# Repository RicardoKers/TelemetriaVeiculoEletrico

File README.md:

# TelemetriaVeiculoEletrico

Projeto da telemetria do veículo elétrico do IFC Luzerna versão 2022

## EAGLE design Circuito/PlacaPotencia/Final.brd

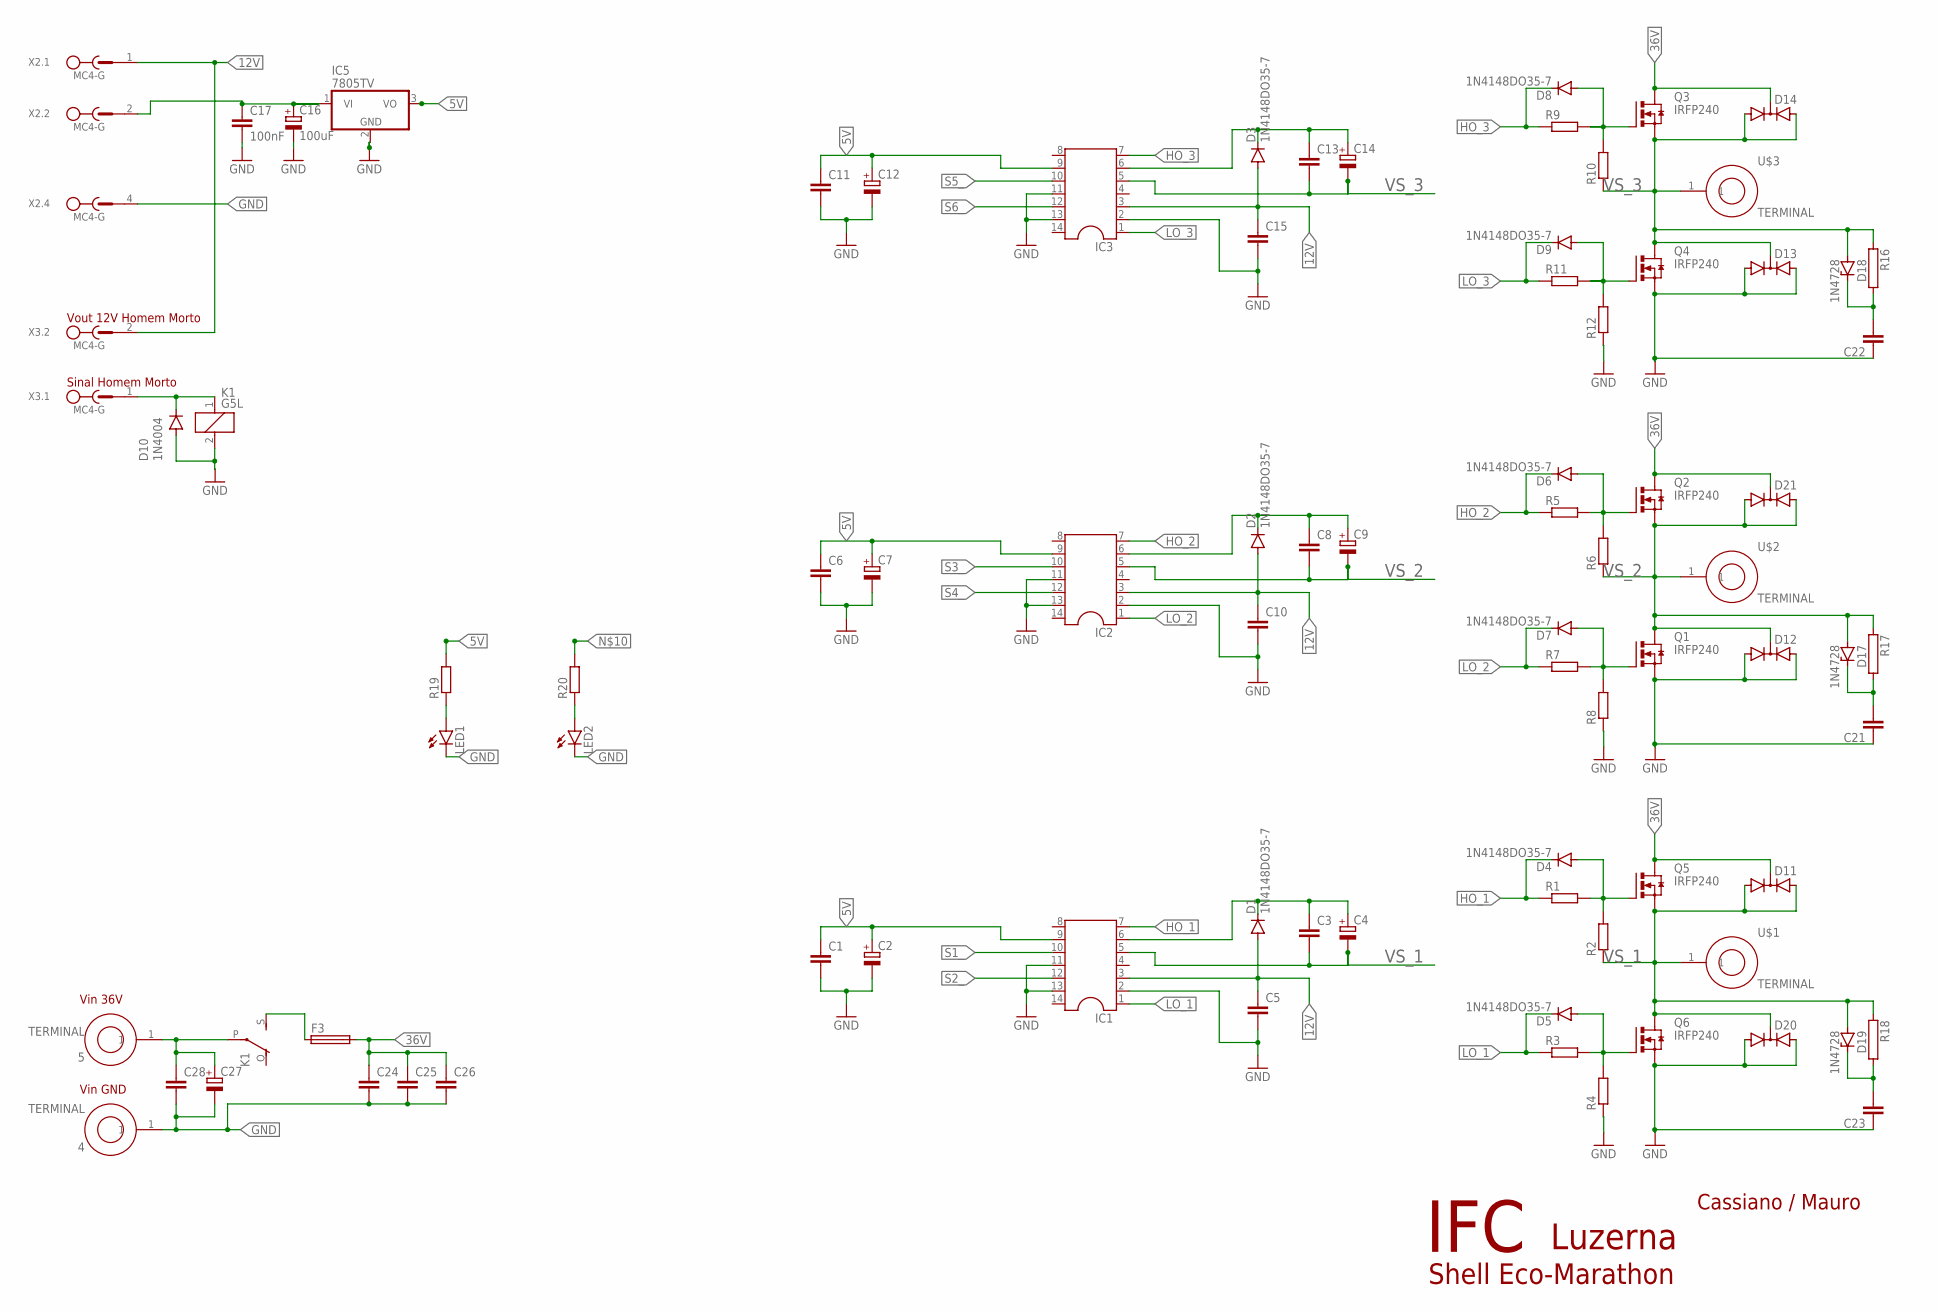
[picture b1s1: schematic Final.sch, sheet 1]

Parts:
4, 5: TERMINAL
C1, C6, C11: C-EU050-045X075; C050-045X075
C2, C4, C7, C9, C12, C14: CPOL-EUE2.5-7; E2,5-7
C3, C5, C8, C10, C13, C15: C-EU050-025X075; C050-025X075
C16: 100uF; E2,5-7
C17: 100nF; C050-045X075
C21, C22, C23: C-EU150-054X183; C150-054X183
C24, C25, C26, C28: C-EU275-093X316; C275-093X316
C27: CPOL-EUE10-22.5; EB22,5D
D1, D2, D3, D4, D5, D6, D7, D8, D9: 1N4148DO35-7; DO35-7
D10: 1N4004; DO41-10
D11, D12, D13, D14, D20, D21: DIODE-2AC|CATO220V; TO220ABS
D17, D18, D19: 1N4728; DO41Z10
F3: SH22,5A
IC1, IC2, IC3: DIL14
IC5: 7805TV; TO220V
K1: G5L; G5LE
LED1, LED2: LED5MM
Q1, Q2, Q3, Q4, Q5, Q6: IRFP240; TO247BV
R1, R2, R3, R4, R5, R6, R7, R8, R9, R10, R11, R12, R19, R20: R-EU_0204/7; 0204/7
R16, R17, R18: RCA4150; CA4150
U$1, U$2, U$3: TERMINAL
X2, X3: MC4-G

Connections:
5V: C1.1, C2.+, C6.1, C7.+, C11.1, C12.+, IC1.9, IC2.9, IC3.9, IC5.3 (VO), R19.2; also elsewhere on the board
12V: C5.1, C10.1, C15.1, D1.A, D2.A, D3.A, IC1.3, IC2.3, IC3.3, X2.1, X3.2
36V: C24.1, C25.1, C26.1, D11.C, D14.C, D21.C, F3.2, Q2.D, Q3.D, Q5.D
GND: 4.1, C1.2, C2.-, C5.2, C6.2, C7.-, C10.2, C11.2, C12.-, C15.2, C16.-, C17.2, C21.1, C22.1, C23.1, C24.2, C25.2, C26.2, C27.-, C28.2, D10.A, D12.A1, D12.A2, D13.A1, D13.A2, D20.A1, D20.A2, IC1.2, IC1.11, IC1.13, IC2.2, IC2.11, IC2.13, IC3.2, IC3.11, IC3.13, IC5.2 (GND), K1.2, LED1.K (C), LED2.K (C), Q1.S, Q4.S, Q6.S, R4.1, R8.1, R12.1, X2.4; also elsewhere on the board
HO_1: D4.C, IC1.7, R1.1
HO_2: D6.C, IC2.7, R5.1
HO_3: D8.C, IC3.7, R9.1
LO_1: D5.C, IC1.1, R3.1
LO_2: D7.C, IC2.1, R7.1
LO_3: D9.C, IC3.1, R11.1
unnamed: D4.A, Q5.G, R1.2, R2.2
unnamed: D5.A, Q6.G, R3.2, R4.2
unnamed: F3.1, K1.S
unnamed: D6.A, Q2.G, R5.2, R6.2
unnamed: D7.A, Q1.G, R7.2, R8.2
unnamed: D8.A, Q3.G, R9.2, R10.2
unnamed: D9.A, Q4.G, R11.2, R12.2
unnamed: C16.+, C17.1, IC5.1 (VI), X2.2
unnamed: D10.C, K1.1, R20.2, X3.1
unnamed: 5.1, C27.+, C28.1, K1.P
unnamed: LED1.A, R19.1
unnamed: LED2.A, R20.1
unnamed: C22.2, D18.C, R16.2
unnamed: C21.2, D17.C, R17.2
unnamed: C23.2, D19.C, R18.2
S1_: IC1.10; also elsewhere on the board
S2_: IC1.12; also elsewhere on the board
S3_: IC2.10; also elsewhere on the board
S4_: IC2.12; also elsewhere on the board
S5_: IC3.10; also elsewhere on the board
S6_: IC3.12; also elsewhere on the board
VB_1: C3.1, C4.+, D1.C, IC1.6
VB_2: C8.1, C9.+, D2.C, IC2.6
VB_3: C13.1, C14.+, D3.C, IC3.6
VS_1: C3.2, C4.-, D11.A1, D11.A2, D19.A, D20.C, IC1.5, Q5.S, Q6.D, R2.1, R18.1, U$1.1
VS_2: C8.2, C9.-, D12.C, D17.A, D21.A1, D21.A2, IC2.5, Q1.D, Q2.S, R6.1, R17.1, U$2.1
VS_3: C13.2, C14.-, D13.C, D14.A1, D14.A2, D18.A, IC3.5, Q3.S, Q4.D, R10.1, R16.1, U$3.1

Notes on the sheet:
Vout 12V Homem Morto
Sinal Homem Morto
Vin 36V
Vin GND
Shell Eco-Marathon
Cassiano / Mauro
IFC
Luzerna

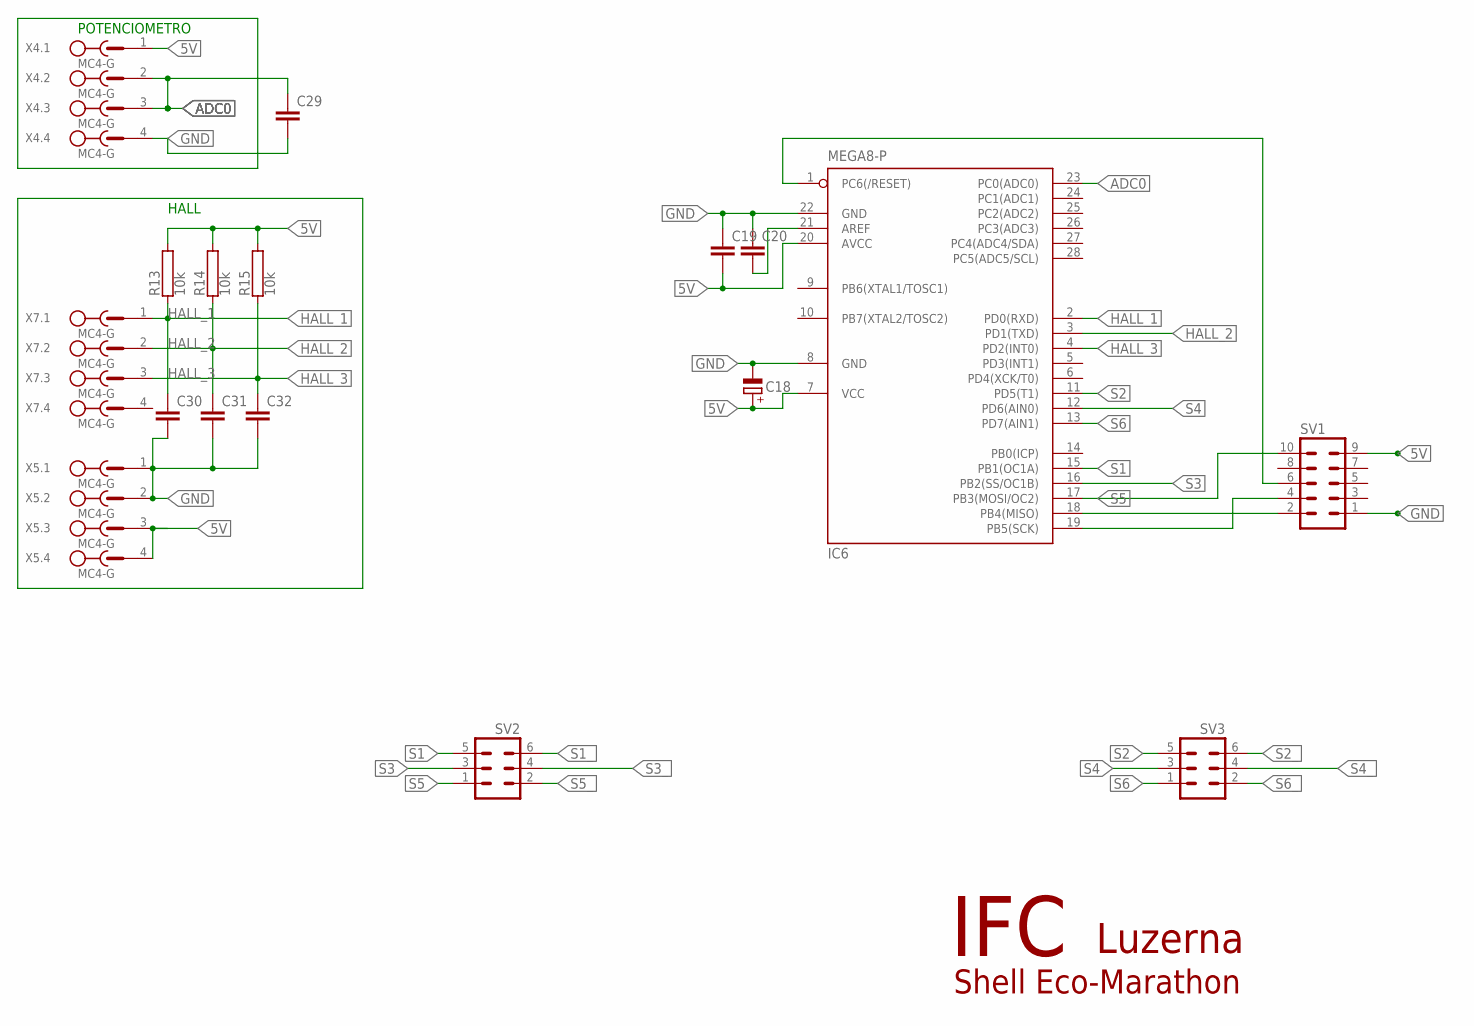
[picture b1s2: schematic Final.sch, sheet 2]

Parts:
C18: CPOL-EUE3.5-10; E3,5-10
C19, C20, C29, C30, C31, C32: C-EU075-032X103; C075-032X103
IC6: MEGA8-P; DIL28-3
R13, R14, R15: 10k; RS1/4
SV1: MA05-2
SV2, SV3: MA03-2
X4, X5, X7: MC4-G

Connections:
5V: C18.+, C19.2, IC6.7 (VCC), IC6.20 (AVCC), R13.2, R14.2, R15.2, SV1.9, X4.1, X5.3, X5.4; also elsewhere on the board
ADC0: C29.1, IC6.23 (PC0(ADC0)), X4.2, X4.3
GND: C18.-, C19.1, C20.1, C29.2, C30.2, C31.2, C32.2, IC6.8 (GND), IC6.22 (GND), SV1.1, X4.4, X5.1, X5.2; also elsewhere on the board
HALL_1: C30.1, IC6.2 (PD0(RXD)), R13.1, X7.1
HALL_2: C31.1, IC6.3 (PD1(TXD)), R14.1, X7.2
HALL_3: C32.1, IC6.4 (PD2(INT0)), R15.1, X7.3
unnamed: C20.2, IC6.21 (AREF)
unnamed: IC6.19 (PB5(SCK)), SV1.4
unnamed: IC6.18 (PB4(MISO)), SV1.2
unnamed: IC6.1 (PC6(/RESET)), SV1.6
S1: IC6.15 (PB1(OC1A)), SV2.5
S1_: SV2.6; also elsewhere on the board
S2: IC6.11 (PD5(T1)), SV3.5
S2_: SV3.6; also elsewhere on the board
S3: IC6.16 (PB2(SS/OC1B)), SV2.3
S3_: SV2.4; also elsewhere on the board
S4: IC6.12 (PD6(AIN0)), SV3.3
S4_: SV3.4; also elsewhere on the board
S5: IC6.17 (PB3(MOSI/OC2)), SV1.10, SV2.1
S5_: SV2.2; also elsewhere on the board
S6: IC6.13 (PD7(AIN1)), SV3.1
S6_: SV3.2; also elsewhere on the board

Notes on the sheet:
POTENCIOMETRO
HALL
Shell Eco-Marathon
IFC
Luzerna

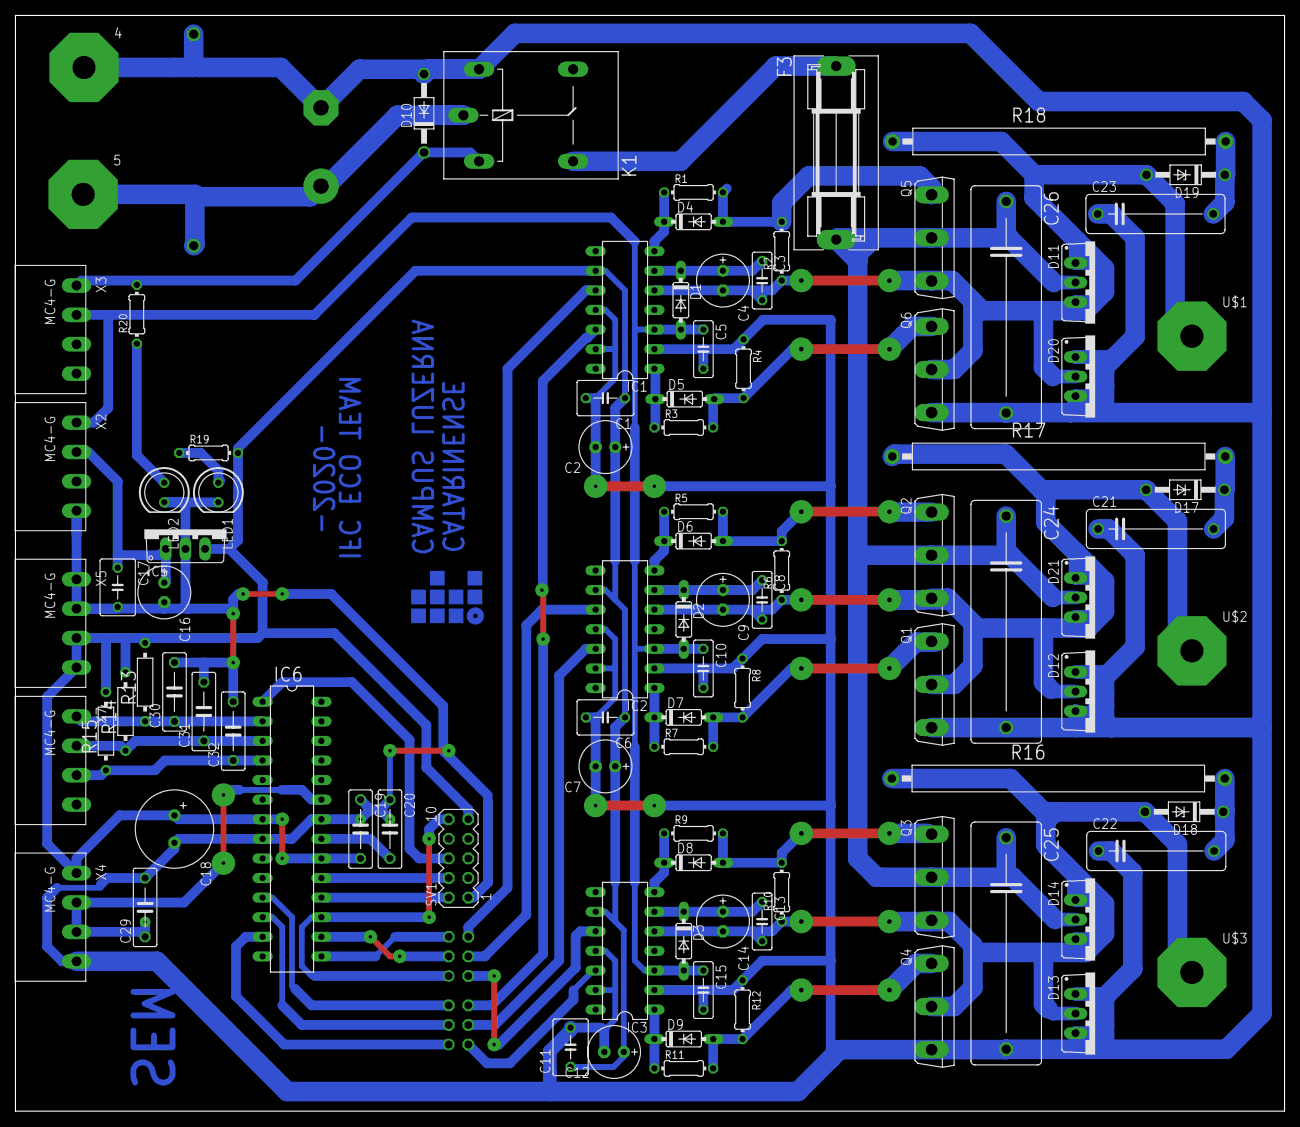
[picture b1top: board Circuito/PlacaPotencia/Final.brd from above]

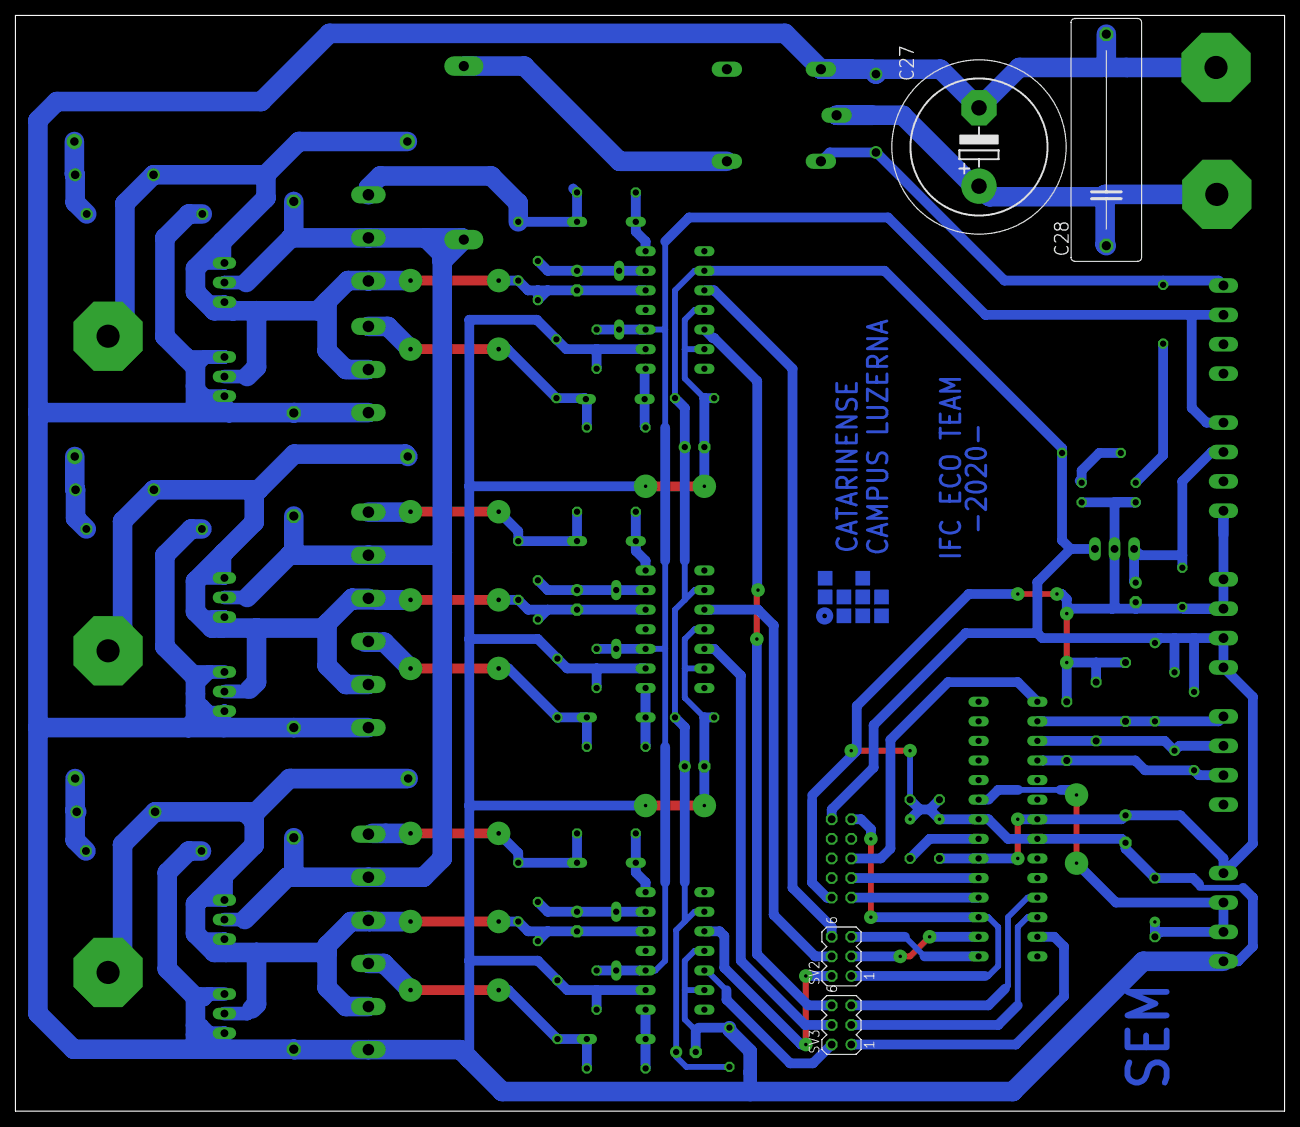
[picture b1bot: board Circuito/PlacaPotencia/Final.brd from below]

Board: 2 copper layers, 164.6 x 142.1 mm, 99 parts (4 on the bottom side), 51 nets.

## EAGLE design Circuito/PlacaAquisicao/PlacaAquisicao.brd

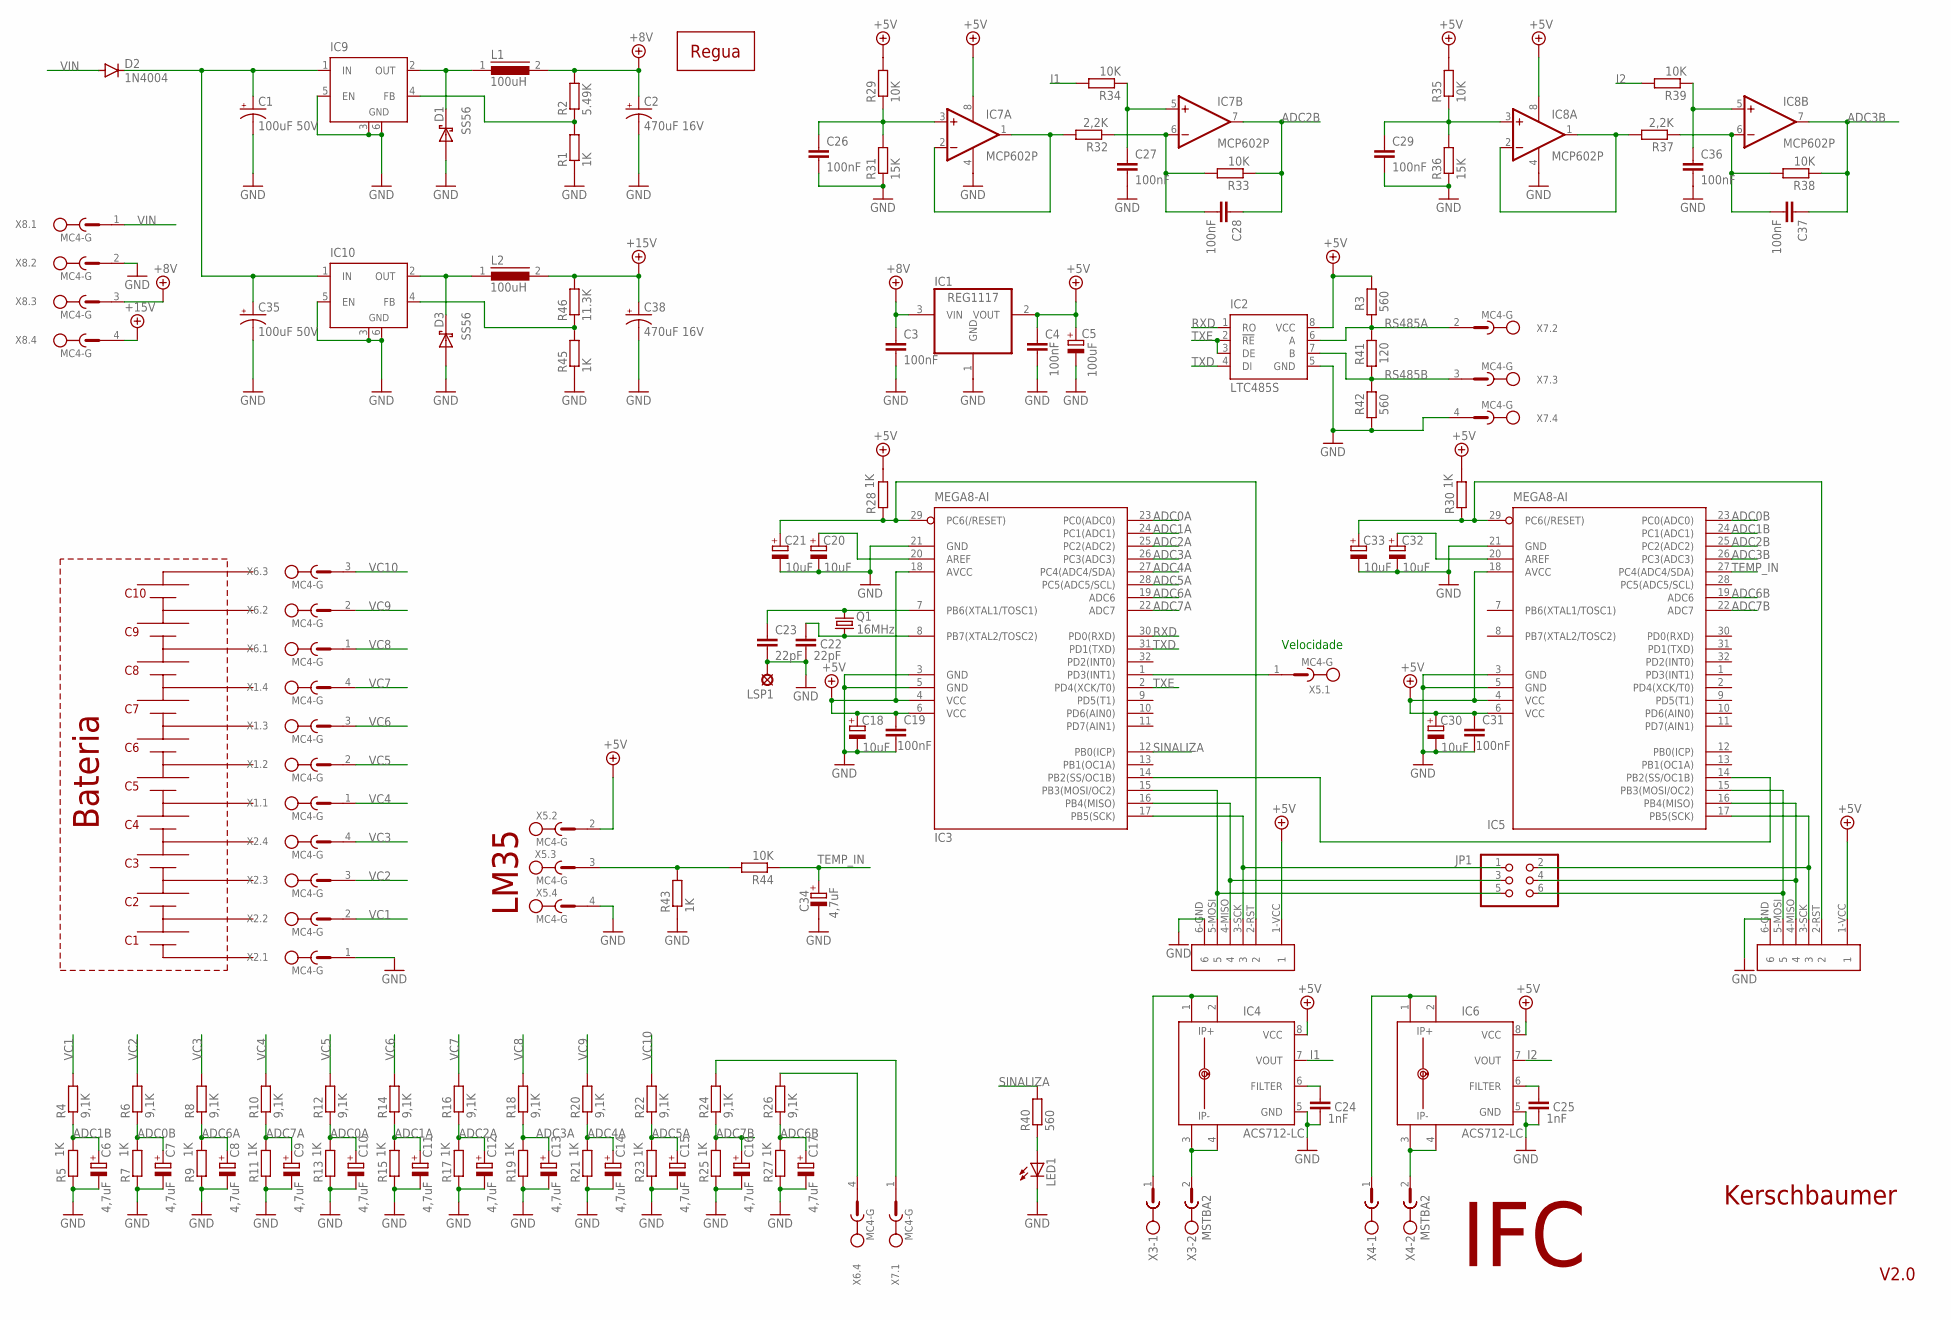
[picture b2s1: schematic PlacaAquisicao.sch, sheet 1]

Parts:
C1, C35: 100uF 50V; E2,5-7
C2, C38: 470uF 16V; E2,5-7
C3, C4, C19, C26, C27, C28, C29, C31, C36, C37: 100nF; C050-025X075
C5: 100uF; E2,5-6
C6, C7, C8, C9, C10, C11, C12, C13, C14, C15, C16, C17, C34: 4,7uF; E2,5-6
C18, C20, C21, C30, C32, C33: 10uF; E2,5-6
C22, C23: 22pF; C025-025X050
C24, C25: 1nF; C025-025X050
D1, D3: SS56; SMA-DIODE
D2: 1N4004; DO41-10
IC1: REG1117; SOT223
IC2: LTC485S; SOIC8
IC3, IC5: MEGA8-AI; TQFP32-08
IC4, IC6: ACS712-LC; SOIC8
IC7, IC8: MCP602P; DIL08
IC9, IC10: LM2596S; TO263-5
JP1: PINHD-2X3; 2X03
L1, L2: 100uH; DR125
LED1: LED3MM
LSP1: LSP10
P1, P2: SPI
Q1: 16MHz; HC49/S
R1, R5, R7, R9, R11, R13, R15, R17, R19, R21, R23, R25, R27, R28, R30, R43, R45: 1K; 0207/7
R2: 5.49K; 0207/7
R3, R40, R42: 560; 0207/7
R4, R6, R8, R10, R12, R14, R16, R18, R20, R22, R24, R26: 9,1K; 0207/7
R29, R33, R34, R35, R38, R39, R44: 10K; 0207/7
R31, R36: 15K; 0207/7
R32, R37: 2,2K; 0207/7
R41: 120; 0207/7
R46: 11.3K; 0207/7
U$1: REGUA
X1, X2, X5, X6, X7, X8: MC4-G
X3, X4: MSTBA2

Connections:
+5V: C4.1, C5.+, C18.+, C19.1, C30.+, C31.1, IC1.2 (VOUT), IC2.8 (VCC), IC3.4 (VCC), IC3.6 (VCC), IC3.18 (AVCC), IC4.8 (VCC), IC5.4 (VCC), IC5.6 (VCC), IC5.18 (AVCC), IC6.8 (VCC), IC7.8 (V+), IC8.8 (V+), P1.1-VCC (1), P2.1-VCC (1), R3.2, R28.2, R29.2, R30.2, R35.2, X5.2
+8V: C2.+, C3.1, IC1.3 (VIN), L1.2, R2.2, X8.3
+15V: C38.+, L2.2, R46.2, X8.4
ADC0A: C10.+, IC3.23 (PC0(ADC0)), R12.1, R13.2
ADC0B: C7.+, IC5.23 (PC0(ADC0)), R6.1, R7.2
ADC1A: C11.+, IC3.24 (PC1(ADC1)), R14.1, R15.2
ADC1B: C6.+, IC5.24 (PC1(ADC1)), R4.1, R5.2
ADC2A: C12.+, IC3.25 (PC2(ADC2)), R16.1, R17.2
ADC2B: C28.1, IC5.25 (PC2(ADC2)), IC7.7 (OUT), R33.1
ADC3A: C13.+, IC3.26 (PC3(ADC3)), R18.1, R19.2
ADC3B: C37.1, IC5.26 (PC3(ADC3)), IC8.7 (OUT), R38.1
ADC4A: C14.+, IC3.27 (PC4(ADC4/SDA)), R20.1, R21.2
ADC5A: C15.+, IC3.28 (PC5(ADC5/SCL)), R22.1, R23.2
ADC6A: C8.+, IC3.19 (ADC6), R8.1, R9.2
ADC6B: C17.+, IC5.19 (ADC6), R26.1, R27.2
ADC7A: C9.+, IC3.22 (ADC7), R10.1, R11.2
ADC7B: C16.+, IC5.22 (ADC7), R24.1, R25.2
GND: C1.-, C2.-, C3.2, C4.2, C5.-, C6.-, C7.-, C8.-, C9.-, C10.-, C11.-, C12.-, C13.-, C14.-, C15.-, C16.-, C17.-, C18.-, C19.2, C20.-, C21.-, C22.2, C23.2, C24.2, C25.2, C26.2, C27.2, C29.2, C30.-, C31.2, C32.-, C33.-, C34.-, C35.-, C36.2, C38.-, D1.A, D3.A, IC1.1 (GND), IC2.5 (GND), IC3.3 (GND), IC3.5 (GND), IC3.21 (GND), IC4.5 (GND), IC5.3 (GND), IC5.5 (GND), IC5.21 (GND), IC6.5 (GND), IC7.4 (V-), IC8.4 (V-), IC9.3 (GND), IC9.5 (EN), IC9.6 (GND), IC10.3 (GND), IC10.5 (EN), IC10.6 (GND), LED1.K (C), LSP1.MP, P1.6-GND (6), P2.6-GND (6), R1.1, R5.1, R7.1, R9.1, R11.1, R13.1, R15.1, R17.1, R19.1, R21.1, R23.1, R25.1, R27.1, R31.1, R36.1, R42.1, R43.1, R45.1, X2.1, X5.4, X7.4, X8.2
I1: IC4.7 (VOUT), R34.2
I2: IC6.7 (VOUT), R39.2
unnamed: C1.+, C35.+, D2.C, IC9.1 (IN), IC10.1 (IN)
unnamed: IC9.4 (FB), R1.2, R2.1
unnamed: D1.C, IC9.2 (OUT), L1.1
unnamed: C20.+, IC3.20 (AREF)
unnamed: IC3.14 (PB2(SS/OC1B)), IC5.14 (PB2(SS/OC1B))
unnamed: C23.1, IC3.7 (PB6(XTAL1/TOSC1)), Q1.2
unnamed: C22.1, IC3.8 (PB7(XTAL2/TOSC2)), Q1.1
unnamed: C21.+, IC3.29 (PC6(/RESET)), P1.2-RST (2), R28.1
unnamed: IC4.3 (IP-), IC4.4 (IP-1), X3.2
unnamed: R26.2, X6.4
unnamed: IC6.3 (IP-), IC6.4 (IP-1), X4.2
unnamed: IC6.1 (IP+), IC6.2 (IP+1), X4.1
unnamed: C24.1, IC4.6 (FILTER)
unnamed: C32.+, IC5.20 (AREF)
unnamed: IC3.17 (PB5(SCK)), JP1.1, P1.3-SCK (3)
unnamed: IC3.16 (PB4(MISO)), JP1.3, P1.4-MISO (4)
unnamed: C33.+, IC5.29 (PC6(/RESET)), P2.2-RST (2), R30.1
unnamed: IC4.1 (IP+), IC4.2 (IP+1), X3.1
unnamed: C25.1, IC6.6 (FILTER)
unnamed: IC3.1 (PD3(INT1)), X5.1
unnamed: R24.2, X7.1
unnamed: IC7.1 (OUT), IC7.2 (-IN), R32.2
unnamed: C26.1, IC7.3 (+IN), R29.1, R31.2
unnamed: C28.2, IC7.6 (-IN), R32.1, R33.2
unnamed: C27.1, IC7.5 (+IN), R34.1
unnamed: IC8.1 (OUT), IC8.2 (-IN), R37.2
unnamed: C29.1, IC8.3 (+IN), R35.1, R36.2
unnamed: C37.2, IC8.6 (-IN), R37.1, R38.2
unnamed: C36.1, IC8.5 (+IN), R39.1
unnamed: IC3.15 (PB3(MOSI/OC2)), JP1.5, P1.5-MOSI (5)
unnamed: LED1.A, R40.1
unnamed: IC5.17 (PB5(SCK)), JP1.2, P2.3-SCK (3)
unnamed: IC5.16 (PB4(MISO)), JP1.4, P2.4-MISO (4)
unnamed: IC5.15 (PB3(MOSI/OC2)), JP1.6, P2.5-MOSI (5)
unnamed: R43.2, R44.2, X5.3
unnamed: IC10.4 (FB), R45.2, R46.1
unnamed: D3.C, IC10.2 (OUT), L2.1
RS485A: IC2.6 (A), R3.1, R41.2, X7.2
RS485B: IC2.7 (B), R41.1, R42.2, X7.3
RXD: IC2.1 (RO), IC3.30 (PD0(RXD))
SINALIZA: IC3.12 (PB0(ICP)), R40.2
TEMP_IN: C34.+, IC5.27 (PC4(ADC4/SDA)), R44.1
TXD: IC2.4 (DI), IC3.31 (PD1(TXD))
TXE: IC2.2 (!RE), IC2.3 (DE), IC3.2 (PD4(XCK/T0))
VC1: R4.2, X2.2
VC2: R6.2, X2.3
VC3: R8.2, X2.4
VC4: R10.2, X1.1
VC5: R12.2, X1.2
VC6: R14.2, X1.3
VC7: R16.2, X1.4
VC8: R18.2, X6.1
VC9: R20.2, X6.2
VC10: R22.2, X6.3
VIN: D2.A, X8.1

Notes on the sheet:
IFC
Kerschbaumer
C10
Bateria
LM35
Velocidade
V2.0

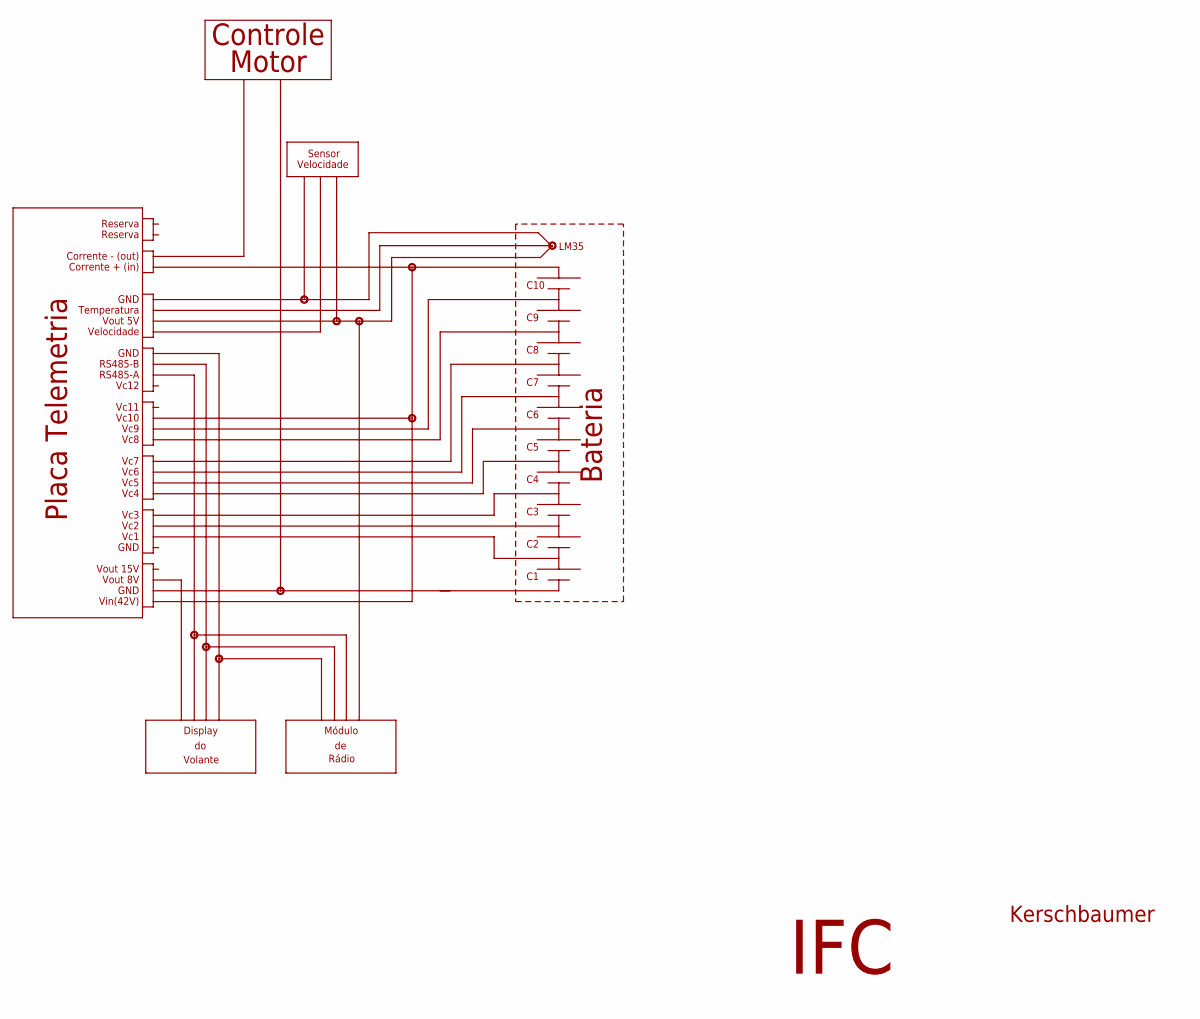
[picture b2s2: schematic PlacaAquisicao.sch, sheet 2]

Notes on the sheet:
IFC
Kerschbaumer
GND
Temperatura
Vout 5V
Velocidade
RS485-B
RS485-A
Vc12
Vc11
Vc10
Vc9
Vc8
Vc7
Vc6
Vc5
Vc4
Vc3
Vc2
Vc1
Vout 15V
Vout 8V
Vin(42V)
Reserva
Corrente - (out)
Corrente + (in)
Placa Telemetria
C10
Bateria
LM35
Controle
Motor
Sensor
Display
Volante
Módulo
Rádio

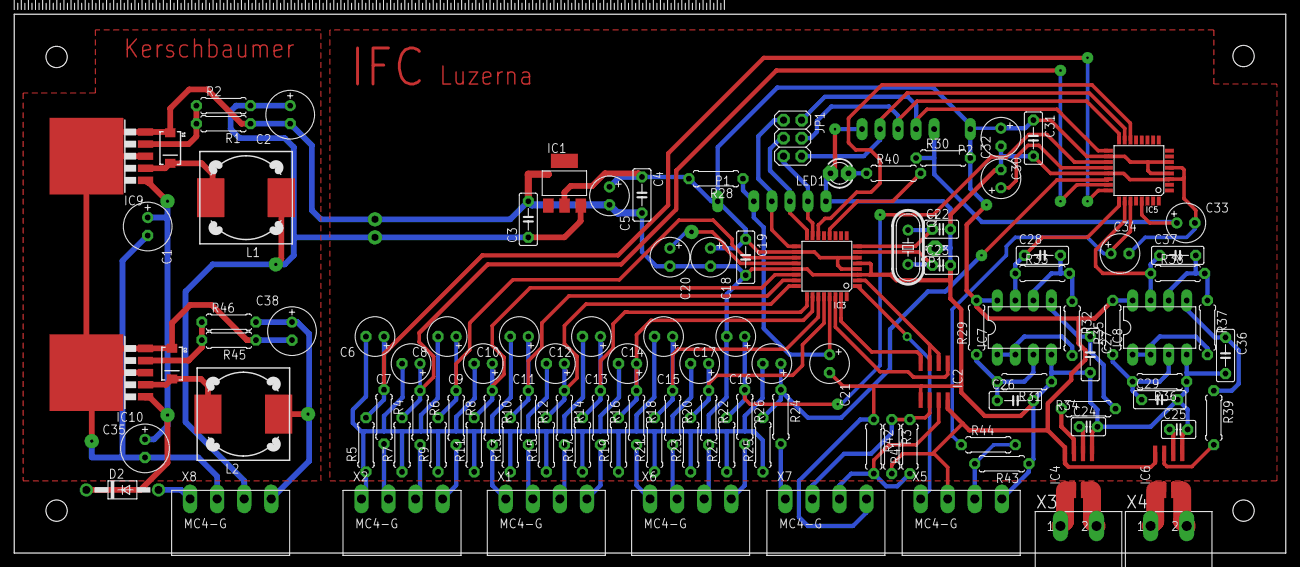
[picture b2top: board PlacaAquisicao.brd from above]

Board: 2 copper layers, 179.1 x 75.9 mm, 114 parts (0 on the bottom side), 75 nets.

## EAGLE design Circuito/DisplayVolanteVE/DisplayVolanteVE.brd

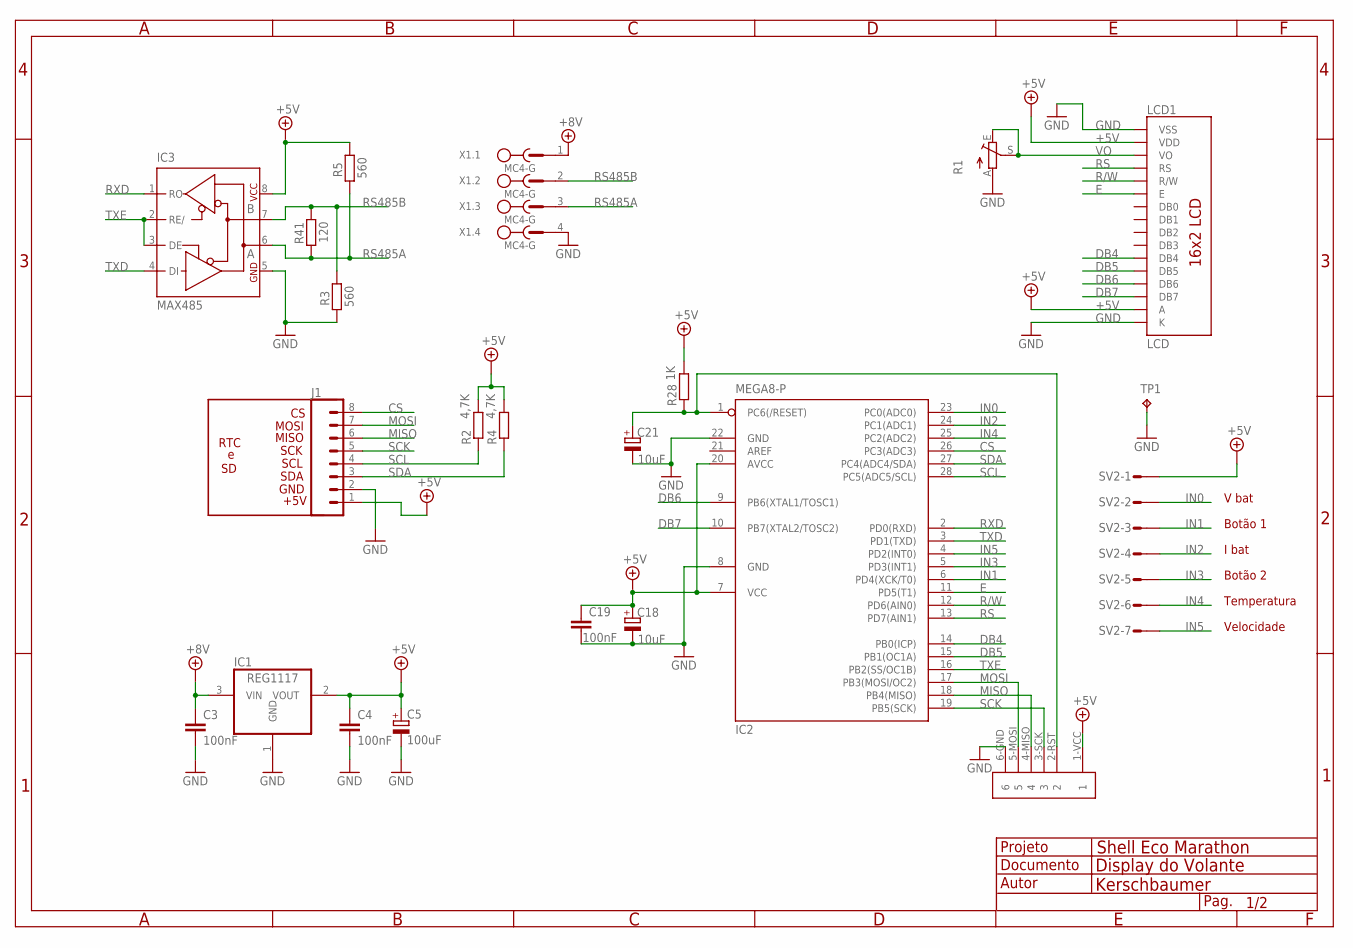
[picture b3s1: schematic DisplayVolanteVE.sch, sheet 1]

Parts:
C3, C4, C19: 100nF; C050-025X075
C5: 100uF; E2,5-6
C18, C21: 10uF; E2,5-6
IC1: REG1117; SOT223
IC2: MEGA8-P; DIL28-3
IC3: MAX485; DIL08
J1: CONN_08NO_SILK_FEMALE_PTH; 1X08_NO_SILK
LCD1: LCD; LCD-16X2_NOHOLESNOSILK
P1: SPI
R1: TRIM_EU-B64Y; B64Y
R2, R4: 4,7K; 0207/7
R3, R5: 560; 0207/7
R28: 1K; 0207/7
R41: 120; 0207/7
SV2: L07P
TP1: TPPAD1-13; P1-13
X1: MC4-G

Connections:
+5V: C4.1, C5.+, C18.+, C19.1, IC1.2 (VOUT), IC2.7 (VCC), IC2.20 (AVCC), IC3.8 (VCC), J1.1, LCD1.2 (VDD), LCD1.15 (A), P1.1-VCC (1), R2.2, R4.2, R5.2, R28.2, SV2.1
+8V: C3.1, IC1.3 (VIN), X1.1
CS: IC2.26 (PC3(ADC3)), J1.8
DB4: IC2.14 (PB0(ICP)), LCD1.11 (DB4)
DB5: IC2.15 (PB1(OC1A)), LCD1.12 (DB5)
DB6: IC2.9 (PB6(XTAL1/TOSC1)), LCD1.13 (DB6)
DB7: IC2.10 (PB7(XTAL2/TOSC2)), LCD1.14 (DB7)
E: IC2.11 (PD5(T1)), LCD1.6 (E)
GND: C3.2, C4.2, C5.-, C18.-, C19.2, C21.-, IC1.1 (GND), IC2.8 (GND), IC2.22 (GND), IC3.5 (GND), J1.2, LCD1.1 (VSS), LCD1.16 (K), P1.6-GND (6), R1.A, R3.1, TP1.TP, X1.4
IN0: IC2.23 (PC0(ADC0)), SV2.2
IN1: IC2.6 (PD4(XCK/T0)), SV2.3
IN2: IC2.24 (PC1(ADC1)), SV2.4
IN3: IC2.5 (PD3(INT1)), SV2.5
IN4: IC2.25 (PC2(ADC2)), SV2.6
IN5: IC2.4 (PD2(INT0)), SV2.7
MISO: IC2.18 (PB4(MISO)), J1.6, P1.4-MISO (4)
MOSI: IC2.17 (PB3(MOSI/OC2)), J1.7, P1.5-MOSI (5)
unnamed: C21.+, IC2.1 (PC6(/RESET)), P1.2-RST (2), R28.1
R/W: IC2.12 (PD6(AIN0)), LCD1.5 (R/W)
RS: IC2.13 (PD7(AIN1)), LCD1.4 (RS)
RS485A: IC3.6 (A), R5.1, R41.1, X1.3
RS485B: IC3.7 (B), R3.2, R41.2, X1.2
RXD: IC2.2 (PD0(RXD)), IC3.1 (RO)
SCK: IC2.19 (PB5(SCK)), J1.5, P1.3-SCK (3)
SCL: IC2.28 (PC5(ADC5/SCL)), J1.4, R2.1
SDA: IC2.27 (PC4(ADC4/SDA)), J1.3, R4.1
TXD: IC2.3 (PD1(TXD)), IC3.4 (DI)
TXE: IC2.16 (PB2(SS/OC1B)), IC3.2 (RE/), IC3.3 (DE)
VO: LCD1.3 (VO), R1.E, R1.S

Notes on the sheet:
Shell Eco Marathon
Display do Volante
Kerschbaumer
RTC
MOSI
MISO
SCK
SCL
SDA
GND
+5V
Botão 1
V bat
I bat
Botão 2
Temperatura
Velocidade

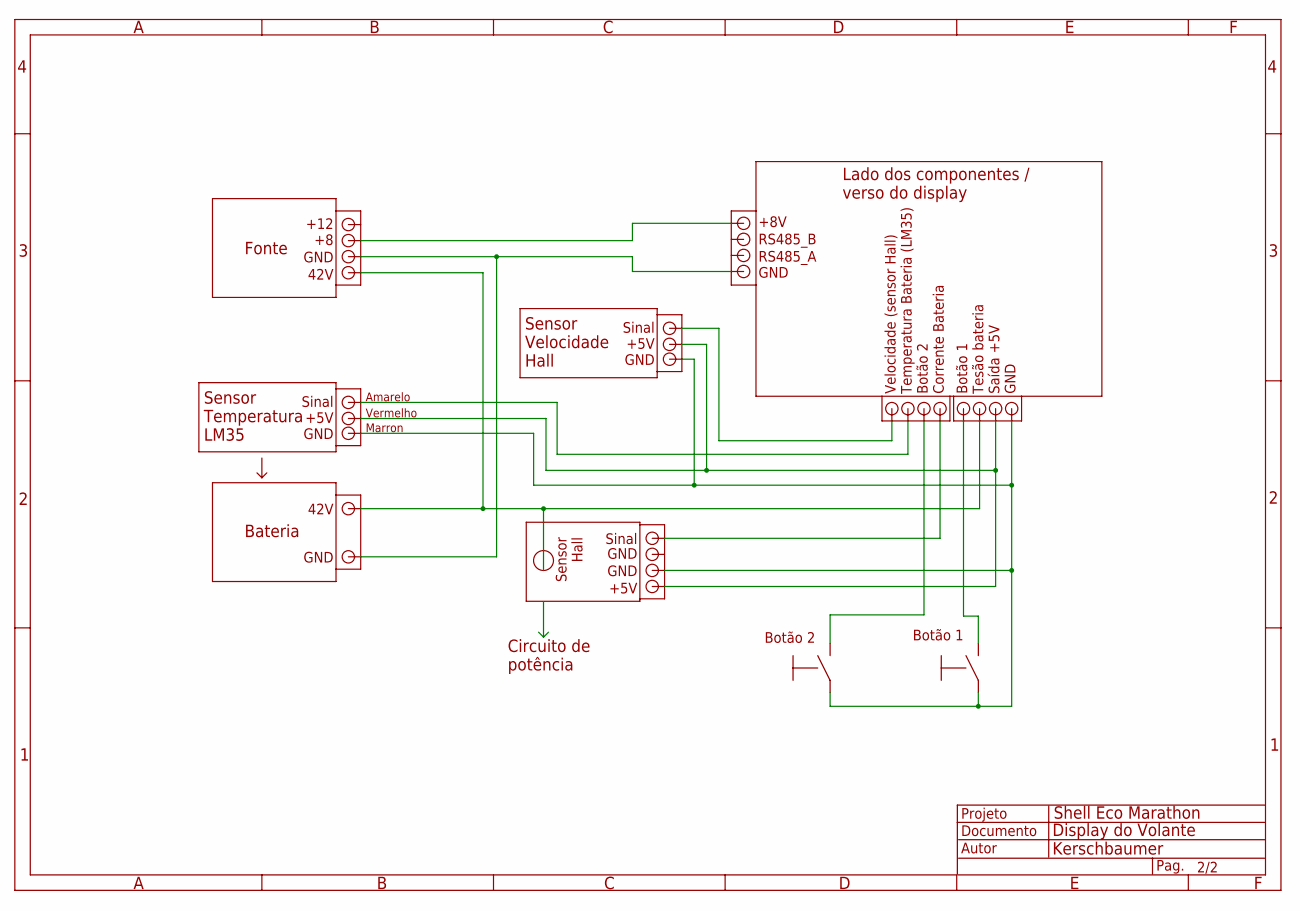
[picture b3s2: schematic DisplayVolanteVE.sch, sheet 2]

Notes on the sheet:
Shell Eco Marathon
Display do Volante
Kerschbaumer
Lado dos componentes / verso do display
+8V
RS485_A
RS485_B
GND
Saída +5V
Tesão bateria
Botão 1
Corrente Bateria
Botão 2
Temperatura Bateria (LM35)
Velocidade (sensor Hall)
42V
+12
Bateria
Fonte
Circuito de potência
Sensor Hall
+5V
Sinal
Sensor Temperatura LM35
Sensor Velocidade Hall
Amarelo
Vermelho
Marron

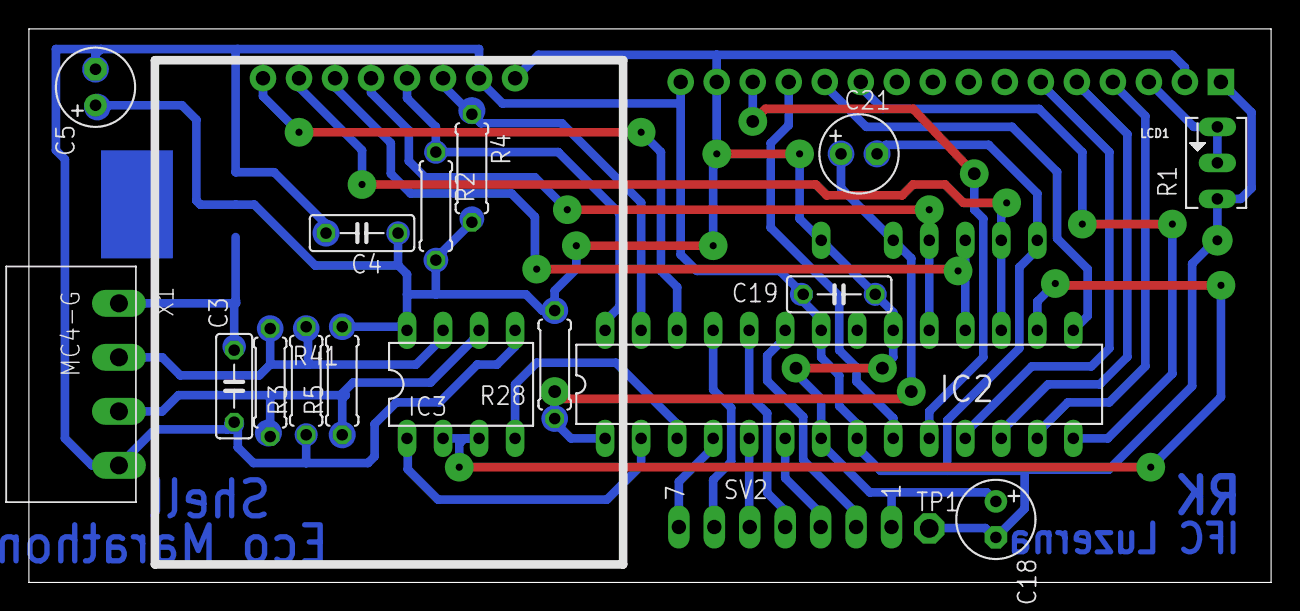
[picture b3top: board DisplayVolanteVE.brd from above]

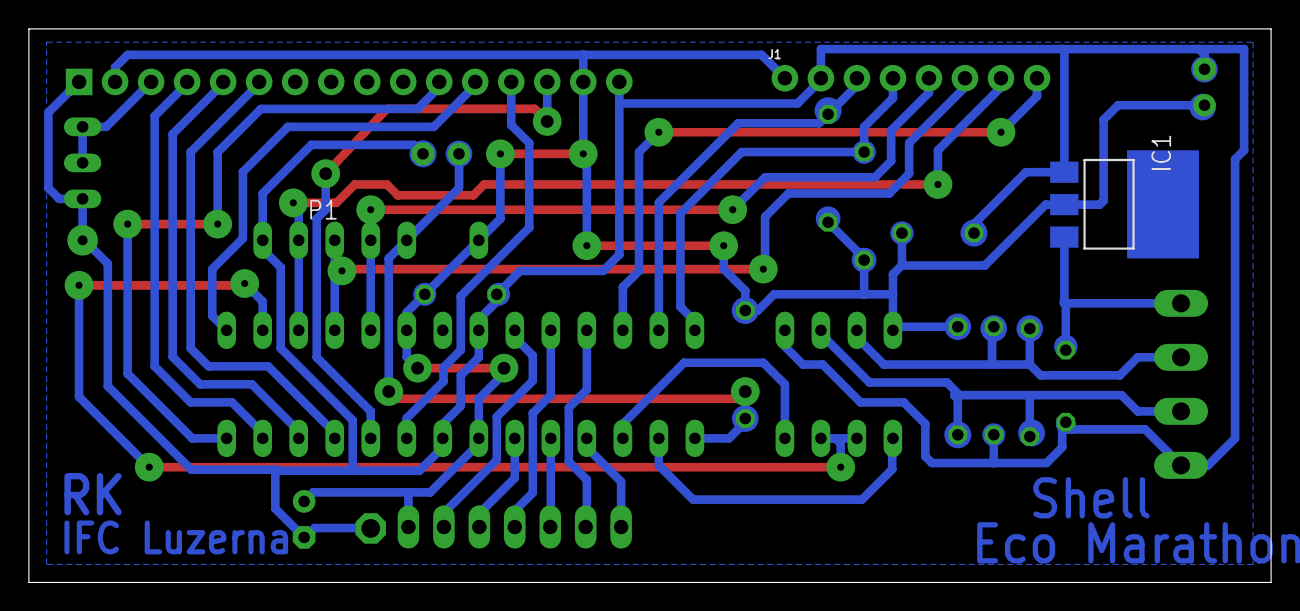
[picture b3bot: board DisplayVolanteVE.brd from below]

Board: 2 copper layers, 87.6 x 39.0 mm, 22 parts (3 on the bottom side), 29 nets.

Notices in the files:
parts and their libraries:
SparkFun-Displays: Licensing: Creative Commons ShareAlike 4.0 International - https://creativecommons.org/licenses/by-sa/4.0
